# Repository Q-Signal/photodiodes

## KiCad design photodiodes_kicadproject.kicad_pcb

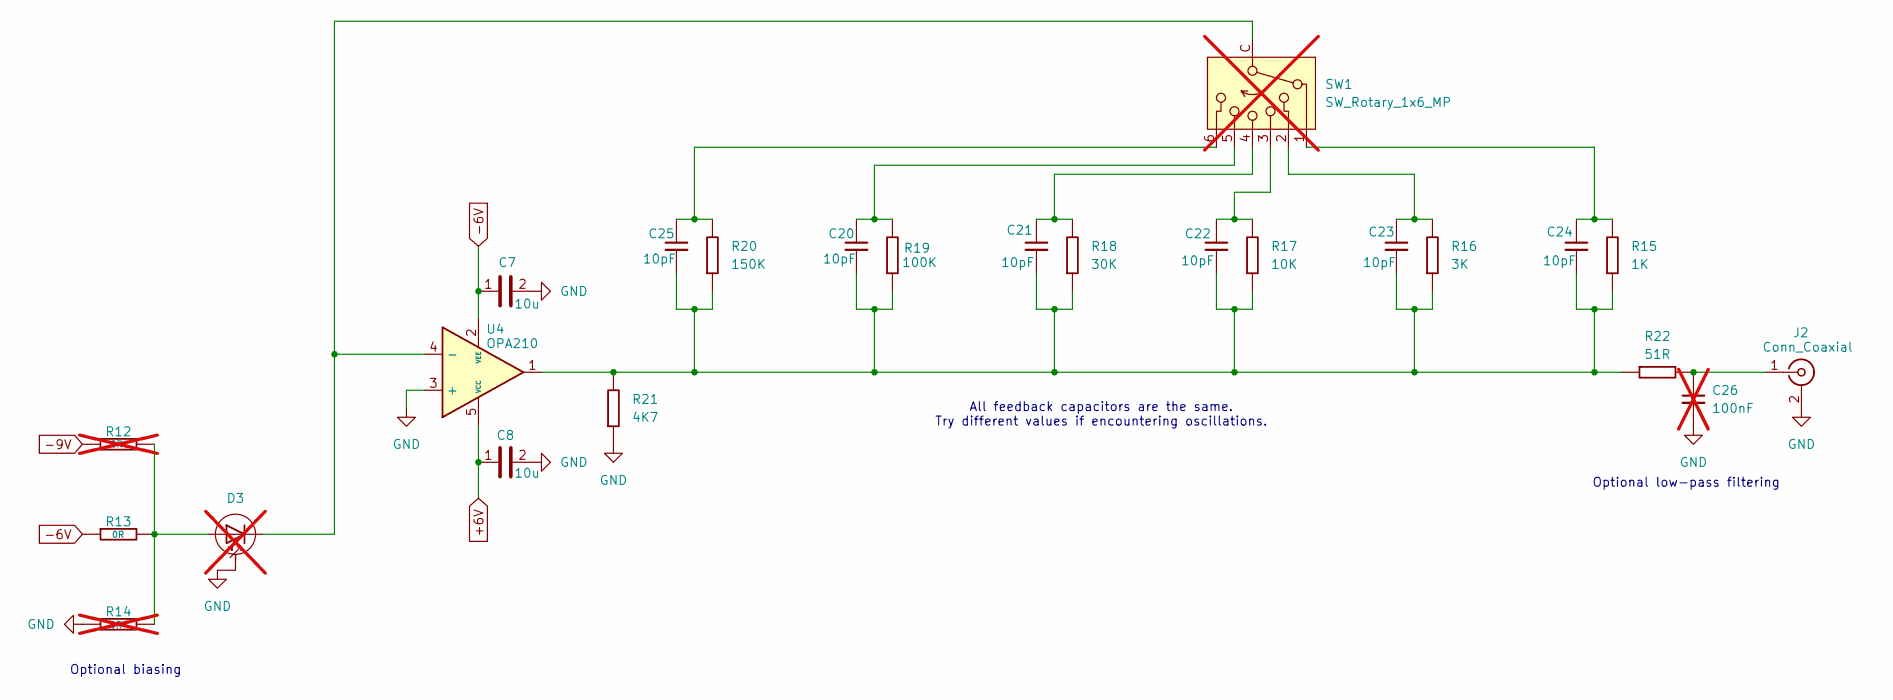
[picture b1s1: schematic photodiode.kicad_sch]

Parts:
C7, C8: 10u; C_0603_1608Metric_Pad1.08x0.95mm_HandSolder; Manufacturer Part Number GRM188R61E106MA73D; DigiKey Part Number 490-7202-2-ND
C20, C21, C22, C23, C24, C25: 10pF; C_0603_1608Metric_Pad1.08x0.95mm_HandSolder; Voltage Rating 50V; Tolerance ±10%; Manufacturer Part Number C0603C100K5RACTU; DigiKey Part Number 399-17562-2-ND
C26: 100nF; C_0603_1608Metric_Pad1.08x0.95mm_HandSolder; Voltage Rating 50V; Tolerance ±10%; Manufacturer Part Number GCJ188R71H104KA12D; DigiKey Part Number 490-5798-2-ND; not fitted
D3: FDS100; Manufacturer Part Number FDS100; not fitted
J2: Conn_Coaxial; BNC_panel_mount
R12, R14: 0R; R_0603_1608Metric_Pad0.98x0.95mm_HandSolder; Manufacturer Part Number RC0603JR-070RL; DigiKey Part Number 311-0.0GRTR-ND; not fitted
R13: 0R; R_0603_1608Metric_Pad0.98x0.95mm_HandSolder; Manufacturer Part Number RC0603JR-070RL; DigiKey Part Number 311-0.0GRTR-ND
R15: 1K; R_0603_1608Metric_Pad0.98x0.95mm_HandSolder; Tolerance 0.01; Manufacturer Part Number RT0603FRE071KL; DigiKey Part Number YAG2323TR-ND
R16: 3K; R_0603_1608Metric_Pad0.98x0.95mm_HandSolder; Tolerance 0.01; Manufacturer Part Number RT0603FRE073KL; DigiKey Part Number 13-RT0603FRE073KLTR-ND
R17: 10K; R_0603_1608Metric_Pad0.98x0.95mm_HandSolder; Tolerance 0.01; Manufacturer Part Number RT0603FRE0710KL; DigiKey Part Number YAG2321TR-ND
R18: 30K; R_0603_1608Metric_Pad0.98x0.95mm_HandSolder; Tolerance 0.01; Manufacturer Part Number RT0603FRE0730KL; DigiKey Part Number 13-RT0603FRE0730KLTR-ND
R19: 100K; R_0603_1608Metric_Pad0.98x0.95mm_HandSolder; Tolerance 0.01; Manufacturer Part Number RT0603FRE13100KL; DigiKey Part Number 13-RT0603FRE13100KLTR-ND
R20: 150K; R_0603_1608Metric_Pad0.98x0.95mm_HandSolder; Tolerance 0.01; Manufacturer Part Number RT0603FRE07150KL; DigiKey Part Number YAG5940TR-ND
R21: 4K7; R_0603_1608Metric_Pad0.98x0.95mm_HandSolder; Tolerance 0.01; Manufacturer Part Number AT0603FRE074K7L; DigiKey Part Number YAG2130TR-ND
R22: 51R; R_0603_1608Metric_Pad0.98x0.95mm_HandSolder; Tolerance 0.01; Manufacturer Part Number RT0603FRE0751RL; DigiKey Part Number 13-RT0603FRE0751RLTR-ND
SW1: SW_Rotary_1x6_MP; C&K_rm_submin_switch; Manufacturer Part Number RM106772BCB; DigiKey Part Number CKN10703-ND; not fitted
U4: OPA210; SOT-23-5_HandSoldering; Manufacturer Part Number OPA210IDBVR; DigiKey Part Number 296-OPA210IDBVRTR-ND

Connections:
+6V: C8.1, U4.5 (VCC); also elsewhere on the board
-6V: C7.1, R13.1, U4.2 (VEE); also elsewhere on the board
-9V: R12.1; also elsewhere on the board
GND: C7.2, C8.2, C26.2, D3.2 (Package), J2.2 (Ext), R14.1, R21.1, U4.3 (+); also elsewhere on the board
unnamed: C20.1, R19.2, SW1.5
unnamed: C20.2, C21.2, C22.2, C23.2, C24.2, C25.2, R15.1, R16.1, R17.1, R18.1, R19.1, R20.1, R21.2, R22.1, U4.1
unnamed: C21.1, R18.2, SW1.4
unnamed: C22.1, R17.2, SW1.3
unnamed: C23.1, R16.2, SW1.2
unnamed: C24.1, R15.2, SW1.1
unnamed: C25.1, R20.2, SW1.6
unnamed: D3.1 (A), R12.2, R13.2, R14.2
unnamed: D3.3 (K), SW1.C, U4.4 (-)
unnamed: C26.1, J2.1 (In), R22.2

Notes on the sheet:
All feedback capacitors are the same. Try different values if encountering oscillations.
Optional biasing
Optional low-pass filtering

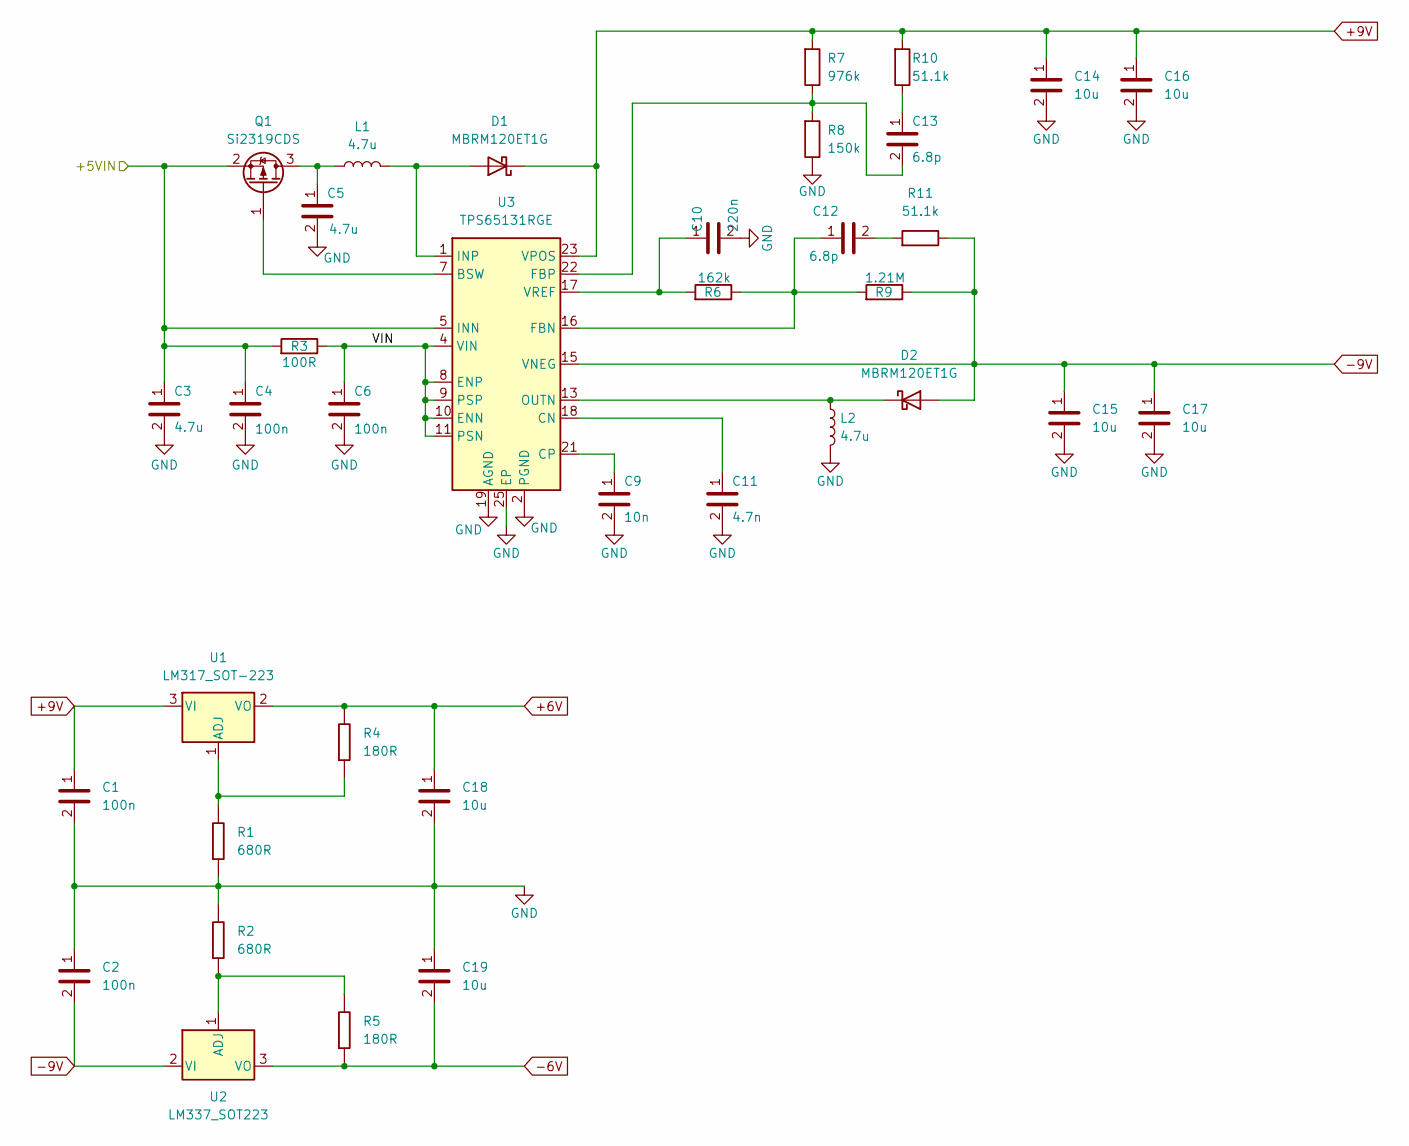
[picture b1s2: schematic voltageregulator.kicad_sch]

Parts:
C1, C2, C4, C6: 100n; C_0402_1005Metric_Pad0.74x0.62mm_HandSolder; Manufacturer Part Number GRM155R71E104KE14D; DigiKey Part Number 490-10698-2-ND
C3, C5: 4.7u; C_0402_1005Metric_Pad0.74x0.62mm_HandSolder; Manufacturer Part Number GRM155R61A475MEAAD; DigiKey Part Number 490-14306-2-ND
C9: 10n; C_0402_1005Metric_Pad0.74x0.62mm_HandSolder; Manufacturer Part Number GRM155R71E103KA01D; DigiKey Part Number 490-1312-2-ND
C10: 220n; C_0402_1005Metric_Pad0.74x0.62mm_HandSolder; Manufacturer Part Number GRT155C81E224KE01D; DigiKey Part Number 490-12245-2-ND
C11: 4.7n; C_0402_1005Metric_Pad0.74x0.62mm_HandSolder; Manufacturer Part Number GRM155R71E472KA01D; DigiKey Part Number 490-1309-2-ND
C12, C13: 6.8p; C_0402_1005Metric_Pad0.74x0.62mm_HandSolder; Manufacturer Part Number GRM1555C1E6R8BA01D; DigiKey Part Number 490-GRM1555C1E6R8BA01DTR-ND
C14, C15, C16, C17, C18, C19: 10u; C_0603_1608Metric_Pad1.08x0.95mm_HandSolder; Manufacturer Part Number GRM188R61E106MA73D; DigiKey Part Number 490-7202-2-ND
D1, D2: MBRM120ET1G; D_Powermite_AK; Manufacturer Part Number MBRM120ET1G; DigiKey Part Number MBRM120ET1GOSTR-ND
L1, L2: 4.7u; L_Bourns_SRP4021HMT; Manufacturer Part Number SRP4021HMT-4R7M; DigiKey Part Number 118-SRP4021HMT-4R7MTR-ND
Q1: Si2319CDS; SOT-23; Manufacturer Part Number SI2319CDS-T1-GE3; DigiKey Part Number SI2319CDS-T1-GE3TR-ND
R1, R2: 680R; R_0603_1608Metric_Pad0.98x0.95mm_HandSolder; Tolerance ±1%; Manufacturer Part Number RT0603FRE13680RL; DigiKey Part Number 13-RT0603FRE13680RLTR-ND
R3: 100R; R_0402_1005Metric_Pad0.72x0.64mm_HandSolder; Manufacturer Part Number RC0402FR-07100RL; DigiKey Part Number 311-100LRTR-ND
R4, R5: 180R; R_0603_1608Metric_Pad0.98x0.95mm_HandSolder; Tolerance ±0.5%; Manufacturer Part Number RT0603DRE07180RL; DigiKey Part Number 311-2448-2-ND
R6: 162k; R_0402_1005Metric_Pad0.72x0.64mm_HandSolder; Manufacturer Part Number RC0402FR-07162KL; DigiKey Part Number YAG2370TR-ND
R7: 976k; R_0402_1005Metric_Pad0.72x0.64mm_HandSolder; Manufacturer Part Number RC0402FR-07976KL; DigiKey Part Number YAG3265TR-ND
R8: 150k; R_0402_1005Metric_Pad0.72x0.64mm_HandSolder; Manufacturer Part Number RC0402FR-07150KL; DigiKey Part Number 311-150KLRTR-ND
R9: 1.21M; R_0402_1005Metric_Pad0.72x0.64mm_HandSolder; Manufacturer Part Number RC0402FR-071M21L; DigiKey Part Number 13-RC0402FR-071M21LTR-ND
R10, R11: 51.1k; R_0402_1005Metric_Pad0.72x0.64mm_HandSolder; Manufacturer Part Number RC0402FR-0751K1L; DigiKey Part Number 311-51.1KLRTR-ND
U1: LM317_SOT-223; SOT-223-3_TabPin2
U2: LM337_SOT223; SOT-223-3_TabPin2
U3: TPS65131RGE; VQFN-24-1EP_4x4mm_P0.5mm_EP2.45x2.45mm_ThermalVias

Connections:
+6V: C18.1, R4.2, U1.2 (VO); also elsewhere on the board
+9V: C1.1, C14.1, C16.1, D1.1 (K), R7.1, R10.1, U1.3 (VI), U3.23 (VPOS)
-6V: C19.2, R5.1, U2.3 (VO); also elsewhere on the board
-9V: C2.2, C15.1, C17.1, D2.2 (A), R9.2, R11.2, U2.2 (VI), U3.15 (VNEG); also elsewhere on the board
/Power Input/+5VIN: C3.1, C4.1, Q1.2 (S), R3.1, U3.5 (INN), U3.6 (INN); also elsewhere on the board
/Voltage Regulator/VIN: C6.1, R3.2, U3.4 (VIN), U3.8 (ENP), U3.9 (PSP), U3.10 (ENN), U3.11 (PSN)
GND: C1.2, C2.1, C3.2, C4.2, C5.2, C6.2, C9.2, C10.2, C11.2, C14.2, C15.2, C16.2, C17.2, C18.2, C19.1, L2.2, R1.1, R2.2, R8.2, U3.2 (PGND), U3.3 (PGND), U3.19 (AGND), U3.25 (EP); also elsewhere on the board
unnamed: C12.2, R11.1
unnamed: C13.1, R10.2
unnamed: D1.2 (A), L1.2, U3.1 (INP), U3.24 (INP)
unnamed: D2.1 (K), L2.1, U3.13 (OUTN), U3.14 (OUTN)
unnamed: C5.1, L1.1, Q1.3 (D)
unnamed: Q1.1 (G), U3.7 (BSW)
unnamed: R1.2, R4.1, U1.1 (ADJ)
unnamed: R2.1, R5.2, U2.1 (ADJ)
unnamed: C11.1, U3.18 (CN)
unnamed: C9.1, U3.21 (CP)
unnamed: C12.1, R6.2, R9.1, U3.16 (FBN)
unnamed: C13.2, R7.2, R8.1, U3.22 (FBP)
unnamed: C10.1, R6.1, U3.17 (VREF)

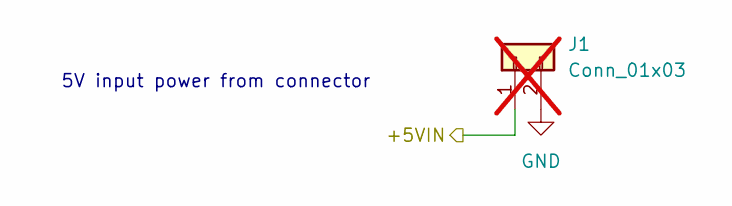
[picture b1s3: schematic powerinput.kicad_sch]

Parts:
J1: Conn_01x03; PinHeader_1x02_P1.27mm_Vertical; not fitted

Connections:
/Power Input/+5VIN: J1.1; also elsewhere on the board
GND: J1.2; also elsewhere on the board

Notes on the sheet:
5V input power from connector

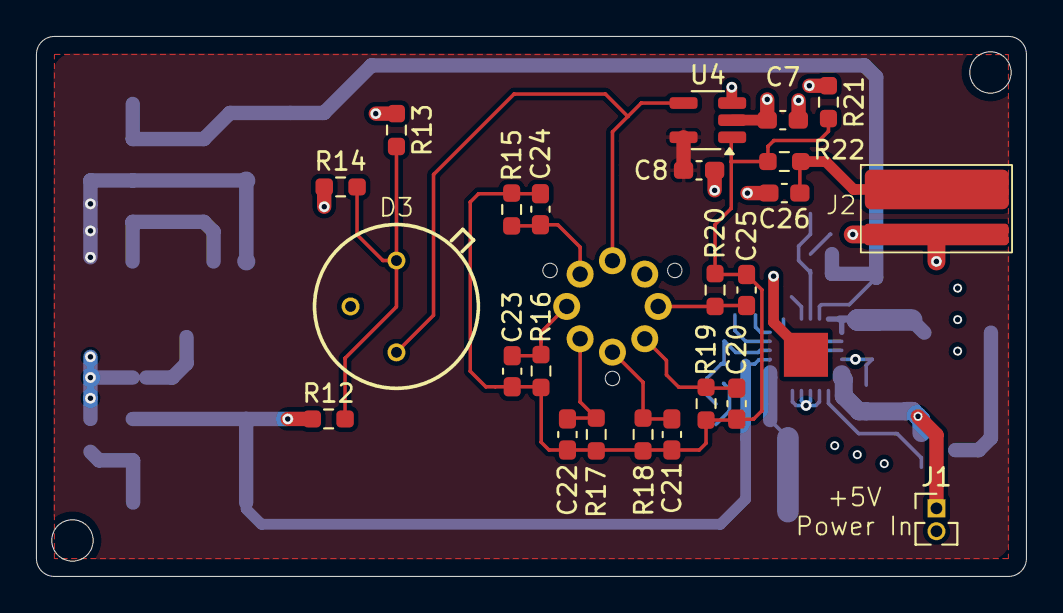
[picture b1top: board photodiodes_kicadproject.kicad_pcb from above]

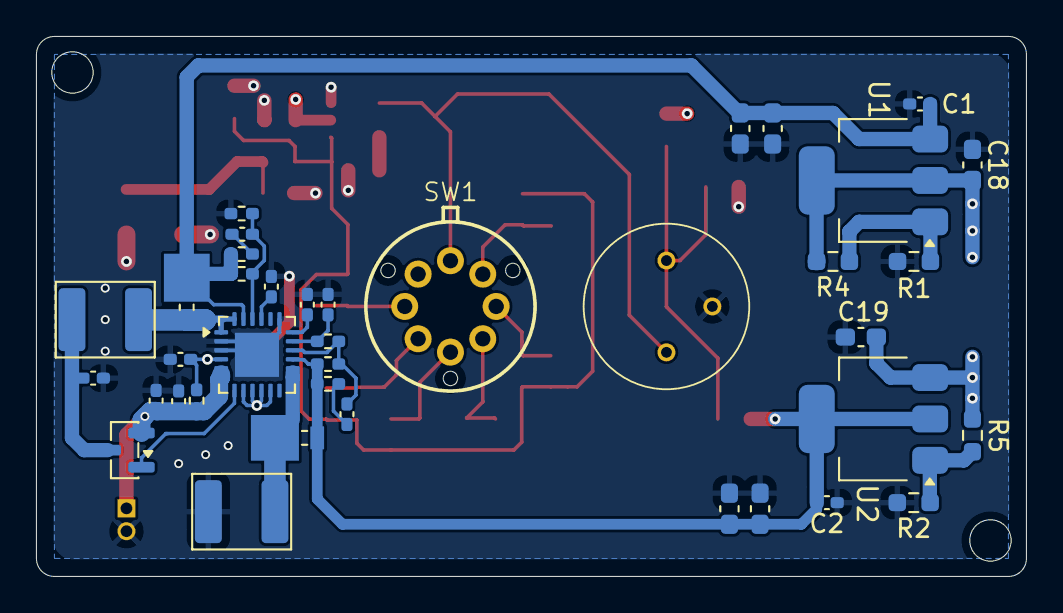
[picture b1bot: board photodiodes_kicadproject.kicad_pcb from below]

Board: 4 copper layers, 55.0 x 30.0 mm, 61 parts (37 on the bottom side), 30 nets.

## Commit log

2026-06-08 Initial commit. Power schematic and routing complete.
2026-06-08 Added license file.
2026-06-09 Added photodiode circuit.
2026-06-09 Added new branch. New branch for different +-9V power supply.
2026-06-09 Save progress.
2026-06-10 Added fabrication files. Board finalized.
2026-06-11 Updated pcb. Added render image. Added pcb step file.
2026-06-11 Updated gerber files.
2026-06-11 Updated fab files.
2026-06-11 Update schematic and pcb. Add fab files.
